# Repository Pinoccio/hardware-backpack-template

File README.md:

pinoccio-backpack-reference
===========================

Contained are the schematics and board layout reference for third-party developed Pinoccio backpacks.

This backpack revision will stay aligned with the board revisions of the Pinoccio hardware, to ensure compatibility.

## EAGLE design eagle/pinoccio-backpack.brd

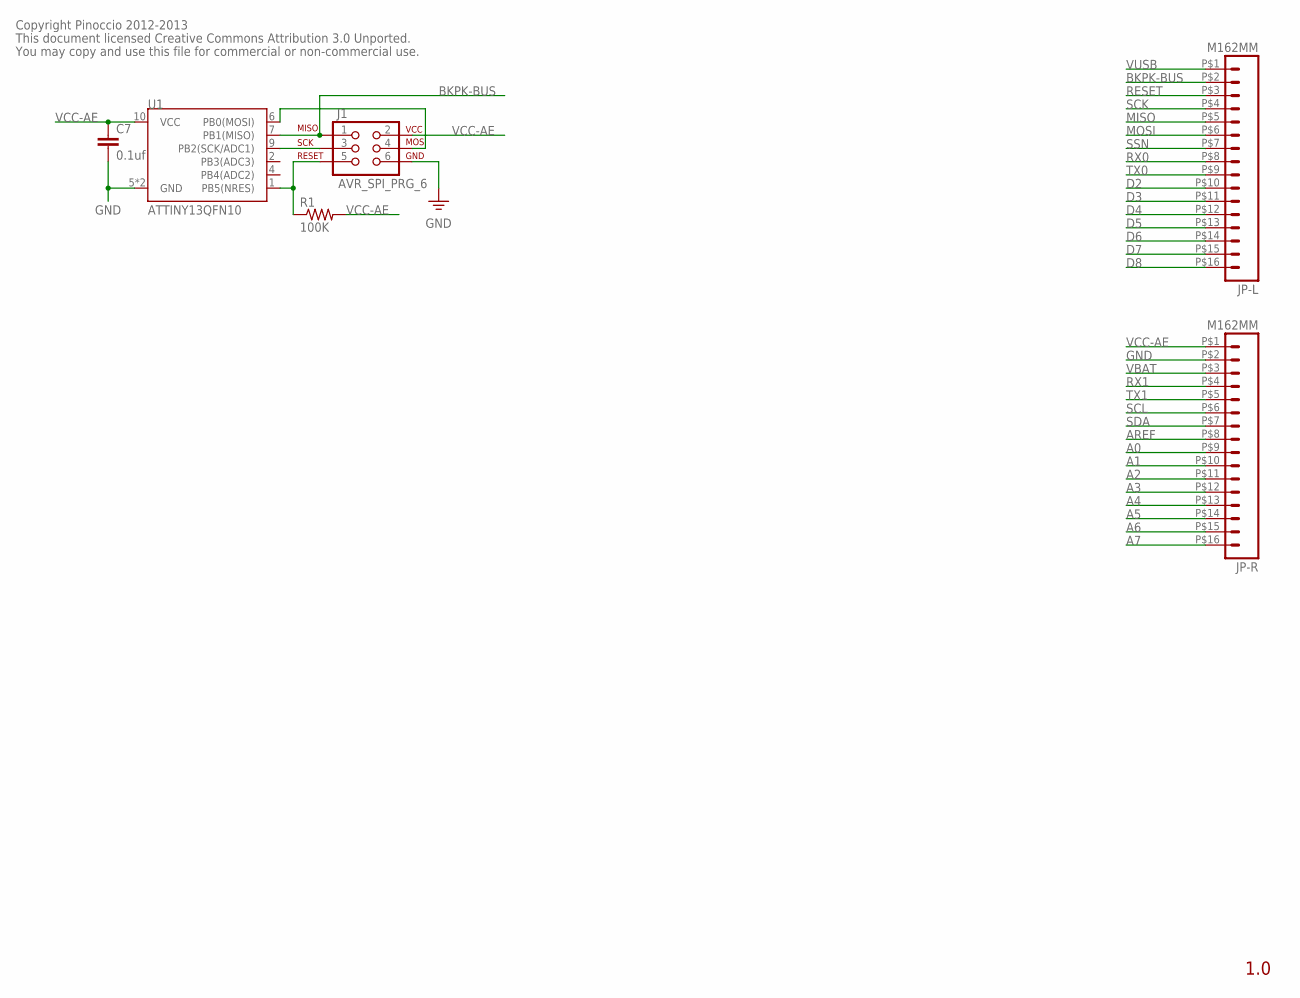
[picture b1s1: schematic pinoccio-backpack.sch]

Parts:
C7: 0.1uf; 0402-CAP
J1: AVR_SPI_PRG_6; 2X3-PAD
JP-L: M162MM; 1X16_2MM
JP-R: M162MM; 1X16_2MM
R1: 100K; 0402-RES
U1: ATTINY13QFN10; QFN-10

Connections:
A0: JP-R.P$9 (9)
A1: JP-R.P$10 (10)
A2: JP-R.P$11 (11)
A3: JP-R.P$12 (12)
A4: JP-R.P$13 (13)
A5: JP-R.P$14 (14)
A6: JP-R.P$15 (15)
A7: JP-R.P$16 (16)
AREF: JP-R.P$8 (8)
BKPK-BUS: J1.1, JP-L.P$2 (2), U1.7 (PB1(MISO))
D2: JP-L.P$10 (10)
D3: JP-L.P$11 (11)
D4: JP-L.P$12 (12)
D5: JP-L.P$13 (13)
D6: JP-L.P$14 (14)
D7: JP-L.P$15 (15)
D8: JP-L.P$16 (16)
GND: C7.2, J1.6, JP-R.P$2 (2), U1.5 (GND), U1.EP (GND)
MISO: JP-L.P$5 (5)
MOSI: JP-L.P$6 (6)
unnamed: J1.4, U1.6 (PB0(MOSI))
unnamed: J1.3, U1.9 (PB2(SCK/ADC1))
unnamed: J1.5, R1.1, U1.1 (PB5(NRES))
RESET: JP-L.P$3 (3)
RX0: JP-L.P$8 (8)
RX1: JP-R.P$4 (4)
SCK: JP-L.P$4 (4)
SCL: JP-R.P$6 (6)
SDA: JP-R.P$7 (7)
SSN: JP-L.P$7 (7)
TX0: JP-L.P$9 (9)
TX1: JP-R.P$5 (5)
VBAT: JP-R.P$3 (3)
VCC-AE: C7.1, J1.2, JP-R.P$1 (1), R1.2, U1.10 (VCC)
VUSB: JP-L.P$1 (1)

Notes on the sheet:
1.0
Copyright Pinoccio 2012-2013
This document licensed Creative Commons Attribution 3.0 Unported.
You may copy and use this file for commercial or non-commercial use.

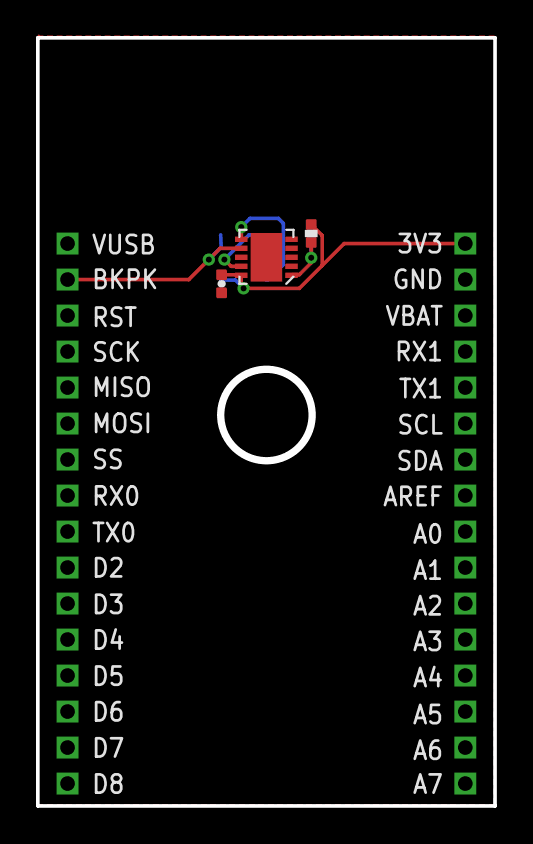
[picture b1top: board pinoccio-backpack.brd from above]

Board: 2 copper layers, 25.2 x 42.5 mm, 6 parts (1 on the bottom side), 6 nets.

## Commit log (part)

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2013-04-26 Updated backpack reference spec
2013-07-24 Updated to v0.13 layout to match latest header location changes
2013-09-26 Added reset pull-up to tiny13
2013-10-24 Revert firmware changes from the last few revisions
    These changes were originally built in separate commits, which I'll
    merge next to preserve all history.
2013-10-31 firmware: Add test sketch for the scout side of the backpack bus
2013-10-31 firmware: Restructure timera code a bit
    This makes the action to be taken by the timera interrupt handler
    explicit in a new global variable. This makes the code a bit more clear.
    Also, currently the shift to the next bit only happens when the timera
    interrupt fires, even though it could sometimes happen in the int0
    interrupt already. Additionally, in some cases the timera interrupt
    doesn't even need to fire (saving power). This change prepares for
2013-10-31 firmware: Remove all default values for global variables
    This saves nearly 20 bytes of flash, since the compiler generates a loop
    that copies data from flash into RAM on reset, which is a lot longer
    than just setting those values in the setup function.
2013-10-31 firmware: Restructure globals section
    This moves all global variables to the same spot, adds comments to some
    enums and renames two constants.
2013-10-31 firmware: Add "make diffdump" command
    This generates assembly stripped of addresses, so it can be used for a
    quick before/after comparison.
2013-10-31 firmware: Initial prototype implementation
2013-10-31 firmware: Implement a STALL/READY bit after each byte
    This allows a slave to stall the master for a while during processing,
    by sending "1" bits (e.g., leave the line floating). When it's done, it
    will send a "0" bit and transmission continues.
2013-10-31 firmware: Remove dependency on TStreaming library
    This library needs avr-gcc 4.7 for c++11 support.
2013-10-31 firmware: Improve debug output a bit
2013-10-31 firmware: Remove useless assignment
2013-10-31 firmware: Rename ACTION_ACK to ACTION_READY
    This bit in the protocol will become stall/ready, the ack bit will
    will be a different bit (if it's added at all).
2013-10-31 firmware: Fix sending of acks after being addressed
2013-10-31 firmware: Add a CFLAGS variable to the Makefile
2013-10-31 firmware: Only mute send and ack/nack bits
    Previously, when FLAG_MUTE was set, all bit sending and sampling was
    suppressed. However, this would also prevent it from sending STALL bits
    or listening to other slaves' stall bits, causing slaves to get out of
    sync sometimes.
2013-10-31 firmware: Don't bother reading the EEPROM while muted
    During bus enumeration, as soon as slaves find out there is another
    slave with a lower id, they'll mute themselves for the remainder of the
    current enumeration round. When this happens, don't bother reading any
    more bytes from EEPROM, they won't be sent anyway.
2013-10-31 firmware: Delay clearing FLAG_MUTE
    Before, the ack/nack bits of the last id byte would not be muted. In
    practice, this wouldn't really matter, since all slaves (muted and
    non-muted) should always send an ACK, but it seems better to make sure
    they are muted anyway.
2013-10-31 firmware: Use stall/ready during enumeration
    This requires inverting the meaning of the stall and ready bits, as well
    as letting each slave that sends a ready bit check the bus for a stall
    bit, in case not all slaves are ready yet.
2013-10-31 firmware: Find out what bit to send earlier
    Instead of at the start of the INT0 ISR (e.g. at the start of a bit
    period), we can now find out what bit to send at the end of the previous
    bit instead. This was not previously possible since sometimes the
    protocol jumped from STALL right into the first bit, without a ready or
    ack bit in between, but this changed so we can now move this code.
    This makes the INT0 ISR even smaller and more single-purpose, which is
2013-10-31 firmware: Add a bunch of comments
2013-10-31 firmware: Fix first unique id byte after muting
    The reading of the EEPROM is skipped when muting, but it should really
    be skipped if the _next_ byte will be muted (e.g. when FLAG_MUTE is set,
    but FLAG_CLEAR_MUTE is not).
2013-10-31 firmware: Tighten timings a bit
    Previously, the timings were relaxed a bit because the slaves couldn't
    always keep up. Now, the slaves do their processing earlier, making it
    less likely the'll be late. Additionally, even if they are late, they
    can now always stall the bus to buy them more time.
2013-10-31 firmware: Also use timer0 overflow interrupt
    This allows splitting the timer events into three separate interrupts:
    output compare A, output compare B and overflow which respectively
    handle sampling the bus, releasing the bus and detecting reset.
    An advantage of this approach is the "next action" handling that happens
    in the COMPA ISR does not have to wait to the end of the bit time for
    a low bit to be released, but can instead always happen either at the
2013-10-31 firmware: Comment cleanup
2013-10-31 firmware: Remove some useless assignments
2013-10-31 firmware: Improve make diffdump
2013-10-31 firmware: Add comments
2013-10-31 firmware: Move protocol constants into protocol.h
    This allows sharing the constants between the firmware and the test
    sketch (even though #include "../protocol.h" isn't very pretty, we can
    fix that later).
2013-10-31 firmware: Invert the parity bit (again)
    This makes sure that reading a byte from an empty bus (all ones) will
    not throw a parity error. Before, when all slaves were enumerated and
    the master would start the final round, it would read all ones and flag
    a parity error. This prevented it from properly detecting the
    "all ones read, enumeration complete" condition, unless some hacks were
    implemented treating all-ones as a special case of parity error.
2013-10-31 firmware: Swap if statement
    This commit does not change behaviour, it just prepares for the next
    change.
2013-10-31 firmware: Move the decision about power down mode
    Before, the overflow handler would set the sleep mode to power down if
    the bus was high. It could do this, since it was certain all timers were
    now disabled. Instead, we now just check the TIMSK0 register before
    going to sleep mode and use power down mode when no timers are running
    (provided the bus is also high, since we can't use an edge-triggered
    interrupt to wake from power down).
2013-11-01 firmware: Let bp_read_bit also report error status
2013-11-04 firmware: Make unique id length 8
    This is the length used by the final specification.
2013-11-04 firmware: Add overview documentation
    Additionallly add or improve some other comments as well.
2013-11-06 tool/EEPROM: Add rough example for the wifi backpack
2013-11-07 docs/EEPROM: Specify the power usage descriptor
    Also update tools/eeprom to know about it.
    The actual format to use for the power usage amps is not defined yet.
2013-11-07 docs/PBBP: Improve error reporting on the bus
    The protocol is now more explicit about how to handle errors. In
    particular:
    - When a slave sends a nack, it should be followed by another byte
    containing an error code.
    - The meaning of this error code can change depending on the current
    command.
2013-11-11 tools/eeprom: Document that it needs python3
2013-11-12 firmware: Enable pullups on unused pins
    This saves some power, since the input logic won't be switching because
    of the floating pins all the time.
2013-11-12 firmware-test: Remember the scan results
    This allows actually using the scan results, but also allows us to print
    the results after the scan. Doing it during the scan caused too long
    delays, so that the transaction would end and only one slave would be
    enumerated.
2013-11-12 firmware-test: Only access EEPROM of enumerated slaves
2013-11-13 firmware-test: Remove EEPROM incrementing code
    There are now some other tests that also do EEPROM writes, so this test
    can be removed for now.
2013-11-13 firmware-test: Use stored eeproms content for write test
    Previously, it used the "b" variable to write an unchanged EEPROM value.
    However, this variable really didn't contain the last EEPROM value
    anymore, since the out-of-bounds read before overwrote its value (even
    though a nack was received). This ensures that the byte really isn't
    changed.
2013-11-13 firmware: Initialize the flags variable
    This variable was left initialized. It probably resets to 0 on powerup,
    but this isn't guaranteed, so better explicitely initialize it.
2013-11-14 firmware: Compile for attiny13a instead of attiny13
    The generated code is effectively the same and compatible, but attiny13a
    has some extra registers we should be using.
    Note that there are some gcc/libc bugs with the attiny13a. One
    workaround is included in the code, another must be implemented on your
    local machine by creating a symlink:
    ln -s /usr/lib/avr/lib/avr25 /usr/lib/avr/lib/avr25/tiny-stack
2013-11-14 firmware: Improve make diffdump output
2013-11-14 firmware: Disable power to the ADC
    We don't need it, so better just disable it altogether, since that
    supposedly saves some power.
2013-11-14 tools/eeprom: Rename wifi upgrade pin to pgm
    This is shorter and better covers the point of the pin.
2013-11-14 tools/eeprom: In the output, include a header per descriptor
2013-11-18 firmware-test: Automatically introduce parity errors
    Instead of just testing a parity error in a single, fixed placed, now
    parity errors are introduced in different stages in the protocol
    automaticallly.
2013-11-18 firmware: Fix indent of protocol.h
2013-11-18 firmware-test: Introduce lengthof macro
2013-11-18 firmware-test: Allow changing inter-bit time
    Previously, only the idle time _after_ a bit was configurable. However,
    when also doing serial printing in between, sometimes the maximum
    inter-bit time would be exceeded. By explicitely checking for this time,
    we can test the limits on it.
2013-11-18 firmware: Prevent triggering INT0 when the slave pulls the line low
    Normally, the line is pulled low before the slave releases the line.
    However, the protocol does not require this, so when the master is using
    minimal timings, it could happen that the line is high before the slave
    pulls it low. In this case, we should prevent triggering INT0 a second
    time.
2013-11-19 firmware-test: Fix base of printed slave error code
2013-11-20 firmware-test: Don't introduce parity errors when nobody is listening
    This would cause an error to be flagged, becaue no parity error would be
    reported, but when there is nobody on the bus, we can't really expect
    them to report a parity error...
2013-11-20 firmware-test: Improve debug output
2013-11-21 docs: Remove spaces from filenames
    GNU make doesn't handle spaces, so this allows us to add a makefile for
    generating the HTML next.
2013-11-22 firmware-test: Show detailed errors on scan failures
2013-11-22 Update backpack bus protocol timings a bit more
    This:
    - Makes the reset pulse longer, so that the maximum inter-bit time can
    become a bit longer. This gives the master a bit more time to do
    processing in between bytes (or bits).
    - Makes the start delay a bit longer. The previous minimum was too
    short, since the slave would not pull the line low before the master
2013-11-22 firmware-test: Write the EEPROM on all detected slaves
2014-01-15 Ignore .swp and .pyc files
2014-01-16 tools/eeprom: Add used eeprom size byte
2014-01-16 firmware-test: Update to new unique id location
2014-01-23 tools/eeprom: Improve validation error output
2014-01-23 docs: Use proper document titles
    By making the first section header of a different type, rst interprets
    it as a document title.
2014-02-13 docs/PBBP: Give hardware revision a major.minor format
    This was already happening in practice, but apparently not actually
    written down.
2014-02-17 tools/eeprom: Update type bytes to match specification
2014-02-17 docs/EEPROM: Reorder the descriptors
    No actual changes were made
2014-02-17 firmware: Rename backpack.c to firmware.c
2014-06-27 firmware-test: Add crc implementation
    These files were already used, but never got added to the repository (so
    the sketch wouldn't compile before).
2014-08-20 Fixed firmware build on Mac OS / *BSD
    Other implementations of head don't support long options like GNU/Linux
    does.

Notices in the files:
eagle/pinoccio-backpack.brd:
Licensed under Creative Commons Attribution 3.0 Unported.
